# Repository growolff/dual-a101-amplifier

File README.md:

# dual_sensor_amp

módulo PCB para amplificar dos sensores Flexiforce A101.

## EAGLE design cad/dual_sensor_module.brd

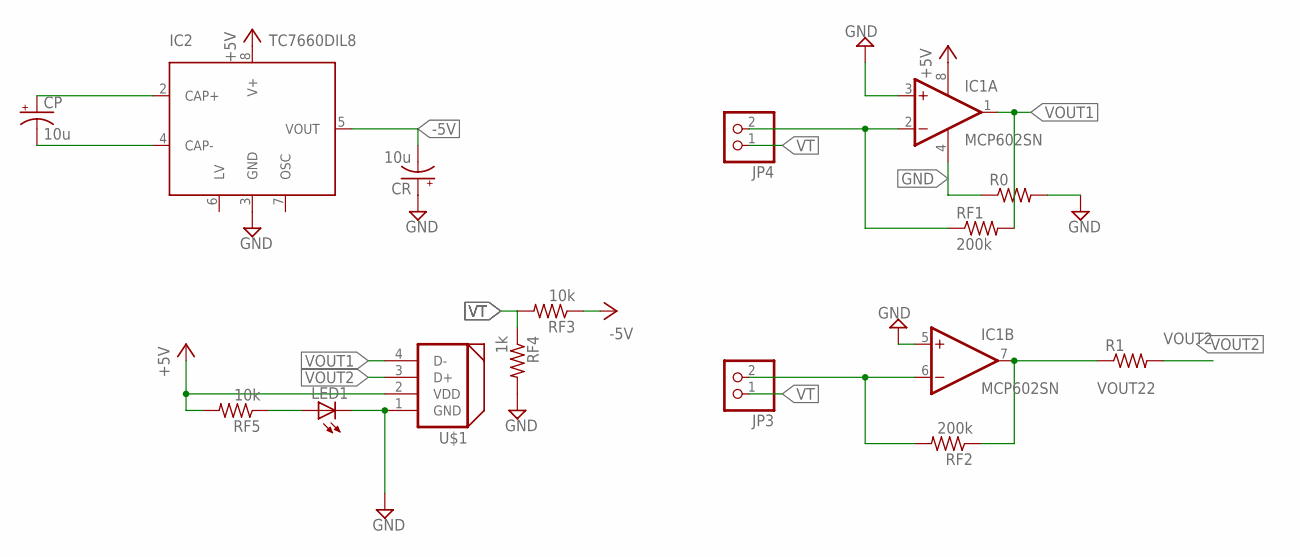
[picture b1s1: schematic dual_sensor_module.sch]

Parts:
CP: 10u; E2,5-5
CR: 10u; E2,5-5
IC1: MCP602SN; SO08
IC2: TC7660DIL8; DIL8
JP3, JP4: PINHD-1X2; 1X02
LED1: LED3MM
R0, R1: R-US_R1206; R1206
RF1, RF2: 200k; R0805
RF3, RF5: 10k; R0805
RF4: 1k; R0805
U$1: DYNAMIXEL_RS485; DYNAMIXEL_SPOX_04

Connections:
+5V: IC1.8 (V+), IC2.8 (V+), RF5.2, U$1.2 (VDD)
-5V: CR.-, IC2.5 (VOUT), RF3.1
GND: CR.+, IC1.3 (+IN), IC1.4 (V-), IC1.5 (+IN), IC2.3 (GND), LED1.K (C), R0.1, R0.2, RF4.2, U$1.1 (GND)
unnamed: CP.+, IC2.2 (CAP+)
unnamed: CP.-, IC2.4 (CAP-)
unnamed: LED1.A, RF5.1
unnamed: IC1.2 (-IN), JP4.2, RF1.1
unnamed: IC1.6 (-IN), JP3.2, RF2.2
VOUT1: IC1.1 (OUT), RF1.2, U$1.4 (D-)
VOUT2: R1.2, U$1.3 (D+)
VOUT22: IC1.7 (OUT), R1.1, RF2.1
VT: JP3.1, JP4.1, RF3.2, RF4.1

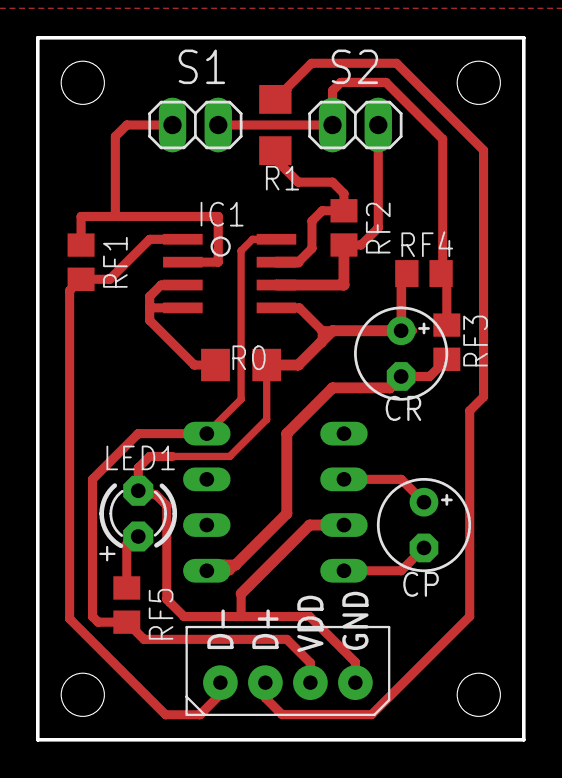
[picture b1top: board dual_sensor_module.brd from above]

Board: 2 copper layers, 27.0 x 39.0 mm, 15 parts (1 on the bottom side), 12 nets.

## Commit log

2020-10-05 v1 dual sensor
2021-08-26 update pcb files
2021-08-26 added arduino test file
